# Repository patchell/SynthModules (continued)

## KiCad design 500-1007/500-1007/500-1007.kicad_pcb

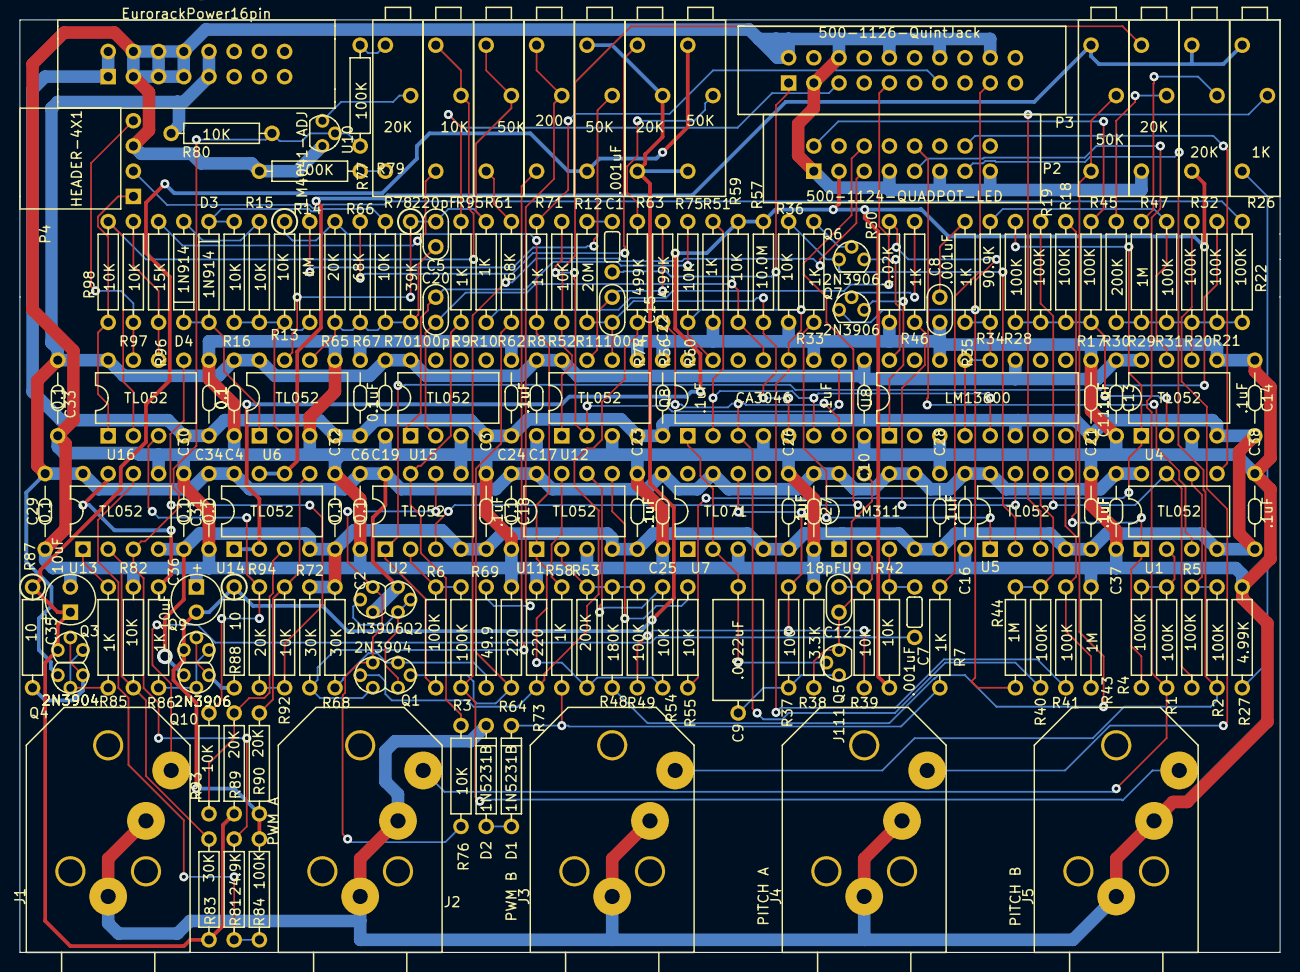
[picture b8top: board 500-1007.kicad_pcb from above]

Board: 2 copper layers, 127.0 x 94.0 mm, 170 parts (0 on the bottom side), 111 nets.

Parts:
C1, C7: .001uF; CAP-GREENIE-0.2
C2, C3, C4, C6, C29, C30, C31, C32, C33, C34: 0.1; CAP-Bypass-0.3
C5: 220pF; CAP-0.1
C8: .001uF; CAP-0.1
C9: .0022uF; CAP-AXIAL-0.5x0.2
C10, C11, C13, C14, C16, C17, C18, C19, C21, C22, C23, C24, C25, C26, C27, C28, C37, C38: .1uF; CAP-Bypass-0.3
C12: 18pF; CAP-0.1
C15, C20: 100pF; CAP-0.1
C35, C36: 10uF; CapPol-Rad-0.2x0.1
D1, D2: 1N5231B; DIODE0.4
D3, D4: 1N914; DIODE0.4
J1: SYNC; PHONE-SC112A
J2: PWM A; PHONE-SC112A
J3: PWM B; PHONE-SC112A
J4: PITCH A; PHONE-SC112A
J5: PITCH B; PHONE-SC112A
P1: EurorackPower16pin; IDC8x2_Vert
P2: 500-1124-QUADPOT-LED; IDC8x2_Vert
P3: 500-1126-QuintJack; IDC10x2_Vert
P4: HEADER-4X1; Header_4Pin_RA_0.1
Q1: 2N3904; DUAL_TO92
Q2: 2N3906; DUAL_TO92
Q3, Q4: 2N3904; TO92
Q5: J111; TO92
Q6, Q7, Q9, Q10: 2N3906; TO92
Q8: CA3046; DIP-14.3
R1, R2, R3, R4, R5, R6, R17, R18, R19, R20, R21, R22, R28, R31, R40, R41, R49, R77, R79, R84: 100K; AXIAL0.4
R7, R8, R9, R10, R33, R35, R46, R51, R58, R85, R86: 1K; AXIAL0.4
R11: 20M; AXIAL0.4
R12, R45, R61, R75: 50K; Trimpot-3006
R13, R15, R16, R36, R39, R42, R52, R54, R55, R59, R60, R67, R76, R80, R82, R92, R93, R97, R98: 10K; AXIAL0.4
R14, R29, R43, R44: 1M; AXIAL0.4
R26: 1K; Trimpot-3006
R27, R56: 4.99K; AXIAL0.4
R30, R53: 200K; AXIAL0.4
R32, R47, R63, R78: 20K; Trimpot-3006
R34: 90.9K; AXIAL0.4
R37: 100; AXIAL0.4
R38: 3.3K; AXIAL0.4
R48: 180K; AXIAL0.4
R50: 4.02K; AXIAL0.4
R57: 10.0M; AXIAL0.4
R62, R66: 68K; AXIAL0.4
R64, R73: 220; AXIAL0.4
R65, R89, R90, R94: 20K; AXIAL0.4
R68, R72, R83: 30K; AXIAL0.4
R69: 49.9; AXIAL0.4
R70: 39K; AXIAL0.4
R71: 200; Trimpot-3006
R74: 499K; AXIAL0.4
R81: 24.9K; AXIAL0.4
R87, R88: 10; AXIAL0.4
R95: 10K; Trimpot-3006
R96: 15K; AXIAL0.4
U1, U2, U4, U5, U6, U11, U12, U13, U14, U15, U16: TL052; DIP8.3
U7: TL071; DIP8.3
U8: LM13600; DIP-16.3
U9: LM311; DIP8.3
U10: LM4041-ADJ; TO92

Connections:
+15V0: C2.1, C4.1, C10.1, C13.1, C16.1, C17.1, C18.1, C19.1, C25.1, C27.1, C29.1, C31.1, C33.1, C37.1, P1.9, P1.10, Q2.1, Q2.4, Q4.3, R80.1, U1.8, U2.8, U4.8, U5.8, U6.8, U7.7, U8.11, U9.5, U9.6, U9.8, U11.8, U12.8, U13.8, U14.8, U15.8, U16.8
-15V0: C3.1, C6.1, C11.1, C14.1, C21.1, C22.1, C23.1, C24.1, C26.1, C28.1, C30.1, C32.1, C34.1, C38.1, P1.1, P1.2, Q10.3, R68.2, R72.2, U1.4, U2.4, U4.4, U5.4, U6.4, U7.4, U8.6, U9.1, U9.4, U11.4, U12.4, U13.4, U14.4, U15.4, U16.4
/Reference/PPOT+: P4.1, R98.1, U16.1
/Reference/PPOT-: P4.4, R97.1, U16.7
/VCO/+5Vr: P2.3, R32.3, R42.2, R57.1, R59.1, U14.1, U14.2
/VCO/-5Vr: R26.1, R32.1, R45.1, U14.6, U14.7
/VCO/LinFM: C1.1, P3.1
/VCO/PULSE: D1.1, R7.1, R58.2
/VCO/PWM1: P2.2, R17.1
/VCO/PWM2: R4.2, R18.1, U1.1
/VCO/PWM3: R5.2, R19.1, U1.7
/VCO/RAMP: R8.1, R13.1, R53.2, R54.1, R65.1, U11.1
/VCO/SYNC: C7.1, J1.3
/VCO/VCO1: J4.3, R20.1
/VCO/VCO2: R6.2, R21.1, U2.1
/VCO/VCO3: P4.2, R22.1
/WaveShaper/+10VR: C35.1, Q3.1, R12.3, R75.1, R83.1, R87.1, R89.2
/WaveShaper/-10vr: C36.2, Q9.1, R12.1, R63.2, R63.3, R75.3, R84.1, R88.2, R90.2
/WaveShaper/SINE: R9.1, R76.2, U2.7
/WaveShaper/TRI: C5.2, R10.1, R61.1, R61.2, R70.2, U6.7
GND: C2.2, C3.2, C4.2, C6.2, C8.2, C10.2, C11.2, C13.2, C14.2, C16.2, C17.2, C18.2, C19.2, C21.2, C22.2, C23.2, C24.2, C25.2, C26.2, C27.2, C28.2, C29.2, C30.2, C31.2, C32.2, C33.2, C34.2, C35.2, C36.1, C37.2, C38.2, D2.1, J1.1, J1.2, J2.1, J2.2, J3.1, J3.2, J4.1, J4.2, J5.1, J5.2, P1.3, P1.4, P1.5, P1.6, P1.7, P1.8, P2.1, P2.7, P2.11, P2.15, P3.2, P3.3, P3.6, P3.10, P3.14, P3.18, P4.3, Q8.4, Q8.9, R27.2, R36.2, R38.2, R43.2, R47.3, R50.2, R51.2, R64.2, R73.2, R79.2, R82.1, U2.5, U4.3, U4.5, U6.3, U6.5, U7.3, U8.3, U8.14, U10.3, U11.3, U12.3, U12.5, U13.5, U15.3
unnamed: C1.2, R11.2
unnamed: C5.1, R65.2, R66.2, R67.2, R70.1, U6.6
unnamed: C7.2, R42.1, U9.3
unnamed: C8.1, R35.2
unnamed: C9.1, Q5.2, Q8.1, U7.2
unnamed: C9.2, Q5.1, R37.1
unnamed: C12.1, R39.2, U9.2
unnamed: C12.2, Q5.3, R38.1, U9.7
unnamed: C15.1, Q8.5, R11.1, R57.2, U12.6
unnamed: C15.2, R56.2, U12.7
unnamed: C20.1, Q8.11, R59.2, U15.2
unnamed: C20.2, R60.2, U15.1
unnamed: D1.2, D2.2
unnamed: D3.1, R16.2, R67.1
unnamed: D3.2, D4.1, U6.1
unnamed: D4.2, R15.2
unnamed: J2.3, P2.9, R1.1
unnamed: J3.3, P2.13, R2.1
unnamed: J5.3, P2.5, R3.1
unnamed: P2.6, U2.3
unnamed: P2.10, U1.3
unnamed: P2.14, U1.5
unnamed: P3.5, R9.2
unnamed: P3.9, R10.2
unnamed: P3.13, R8.2
unnamed: P3.17, R7.2
unnamed: Q1.1, R68.1, R69.1
unnamed: Q1.2, R62.2, R64.1
unnamed: Q1.3, Q2.2, Q2.3, Q2.5
unnamed: Q1.4, R71.3, R72.1
unnamed: Q1.5, R73.1, R74.1
unnamed: Q1.6, Q2.6, R76.1, U2.6
unnamed: Q3.2, Q4.1, R87.2
unnamed: Q3.3, Q4.2, R85.1
unnamed: Q6.1, R36.1, U5.2
unnamed: Q6.2, R33.2
unnamed: Q6.3, U8.16
unnamed: Q7.1, R44.2, R50.1
unnamed: Q7.2, R46.2
unnamed: Q7.3, U8.1
unnamed: Q8.2, Q8.6, R51.1, U8.5
unnamed: Q8.3, Q8.7, R40.1, R56.1
unnamed: Q8.8, R52.2, U12.2
unnamed: Q8.10, Q8.13, R41.1, R60.1
unnamed: Q9.2, Q10.1, R88.1
unnamed: Q9.3, Q10.2, R86.1
unnamed: R1.2, R4.1, U1.2
unnamed: R2.2, R5.1, U1.6
unnamed: R3.2, R6.1, U2.2
unnamed: R12.2, R14.1
unnamed: R13.2, R14.2, R15.1, R16.1, U6.2
unnamed: R17.2, R18.2, R19.2, R28.1, U4.2
unnamed: R20.2, R21.2, R22.2, R29.1, R30.1, R31.1, U4.6
unnamed: R26.2, U5.3
unnamed: R26.3, R27.1
unnamed: R28.2, R55.1, U4.1
unnamed: R29.2, R32.2
unnamed: R30.2, R47.2
unnamed: R31.2, R34.1, U4.7
unnamed: R33.1, U5.1
unnamed: R34.2, R35.1, U8.4, U8.12, U8.13
unnamed: R37.2, R39.1, R49.1, U7.6
unnamed: R40.2, R44.1, U5.6
unnamed: R41.2, R43.1, U5.5
unnamed: R45.2, R45.3, R48.1
unnamed: R46.1, U5.7
unnamed: R47.1, R52.1, U12.1
unnamed: R48.2, R49.2, R53.1, U11.2
unnamed: R54.2, U11.6
unnamed: R55.2, U11.5
unnamed: R58.1, U11.7
unnamed: R61.3, R62.1
unnamed: R63.1, R66.1
unnamed: R69.2, R71.1, R71.2
unnamed: R74.2, R75.2
unnamed: R77.1, R80.2, R81.2, U10.2, U13.3
unnamed: R77.2, R78.1
unnamed: R78.2, U10.1
unnamed: R78.3, R79.1
unnamed: R81.1, R84.2, U13.6
unnamed: R82.2, R83.2, U13.2
unnamed: R85.2, U13.1
unnamed: R86.2, U13.7
unnamed: R89.1, R93.2, U14.3
unnamed: R90.1, R92.2, U14.5
unnamed: R92.1, R94.1, U16.5
unnamed: R93.1, R94.2, U16.3
unnamed: R95.1, R95.2, R98.2, U16.2
unnamed: R95.3, R96.2
unnamed: R96.1, R97.2, U16.6

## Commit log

2021-06-21 Initial Commit
    Synthesizer Modules
